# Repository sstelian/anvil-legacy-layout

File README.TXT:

This repository includes the 3 boards designed for the Anvil sumo robot by Stelian Saracut and Virgil Litan in 2016.

The motor driver board is not functional. The other 2 boards are tested and were previously used on our robot.

Build these boards on your own risk. We do not take responsibility for any damage related to building or using these designs.

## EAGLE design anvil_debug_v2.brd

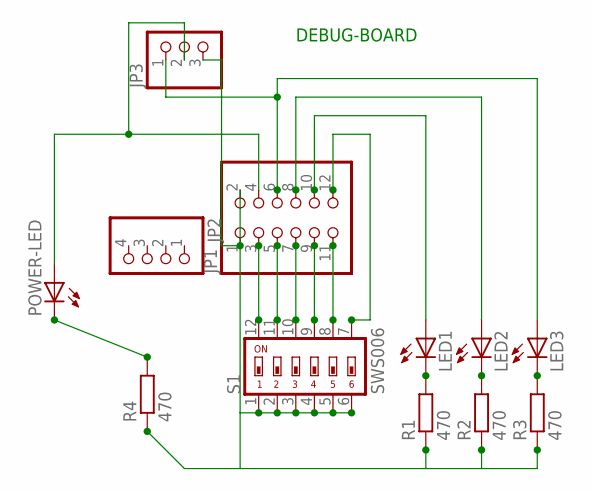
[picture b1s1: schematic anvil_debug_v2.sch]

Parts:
JP1: PINHD-2X6; 2X06
JP2: PINHD-1X4; 1X04
JP3: PINHD-1X3; 1X03
LED1, LED2, LED3: LEDSMT1206; 1206
POWER-LED: LEDSMT1206; 1206
R1, R2, R3, R4: 470; R1206
S1: SWS006; SMS-006

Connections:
unnamed: LED1.C, R1.2
unnamed: LED2.C, R2.2
unnamed: LED3.C, R3.2
unnamed: JP1.3, S1.12
unnamed: JP1.5, S1.11
unnamed: JP1.7, S1.10
unnamed: JP1.9, S1.9
unnamed: JP1.11, S1.8
unnamed: JP1.12, S1.7
unnamed: JP1.10, LED1.A
unnamed: JP1.8, LED2.A
unnamed: JP1.1, JP1.2, JP3.3, R1.1, R2.1, R3.1, R4.1, S1.1, S1.2, S1.3, S1.4, S1.5, S1.6
unnamed: JP1.6, JP3.1, LED3.A
unnamed: POWER-LED.C, R4.2
unnamed: JP1.4, JP3.2, POWER-LED.A

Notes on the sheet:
DEBUG-BOARD

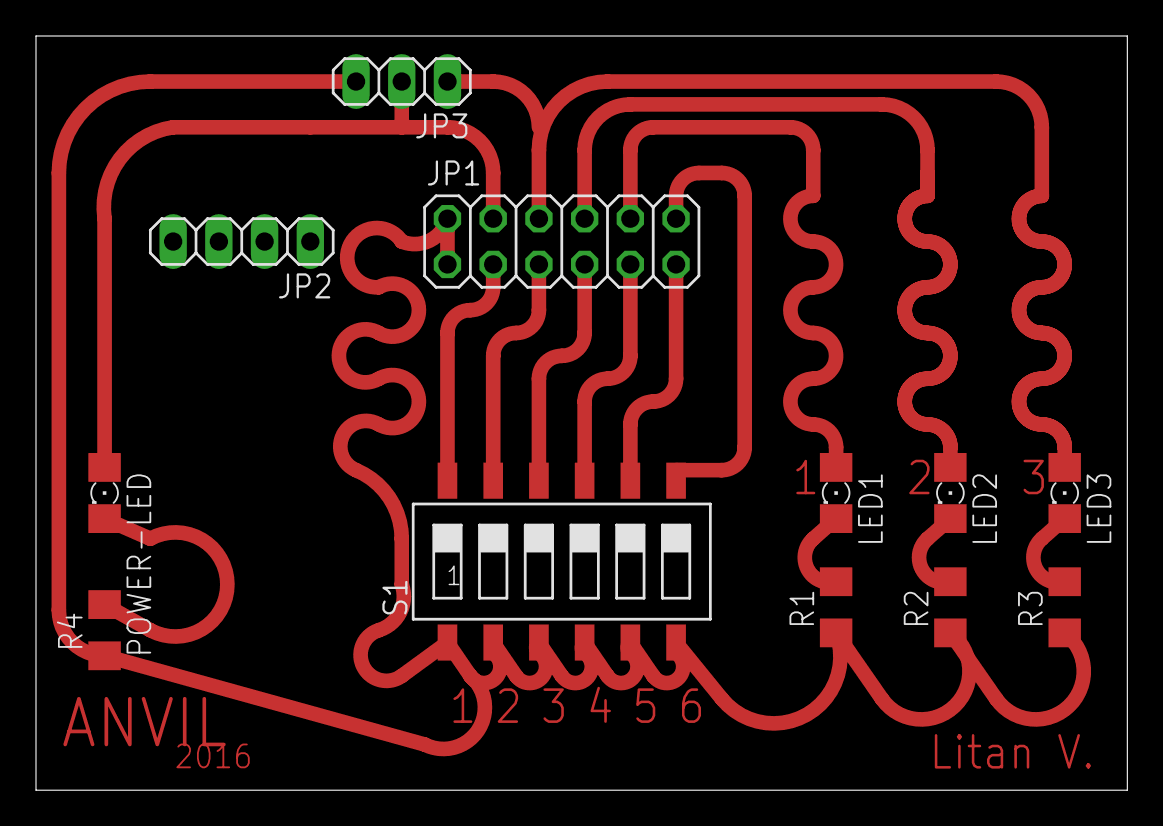
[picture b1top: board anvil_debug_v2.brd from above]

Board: 2 copper layers, 60.6 x 41.9 mm, 12 parts (0 on the bottom side), 15 nets.

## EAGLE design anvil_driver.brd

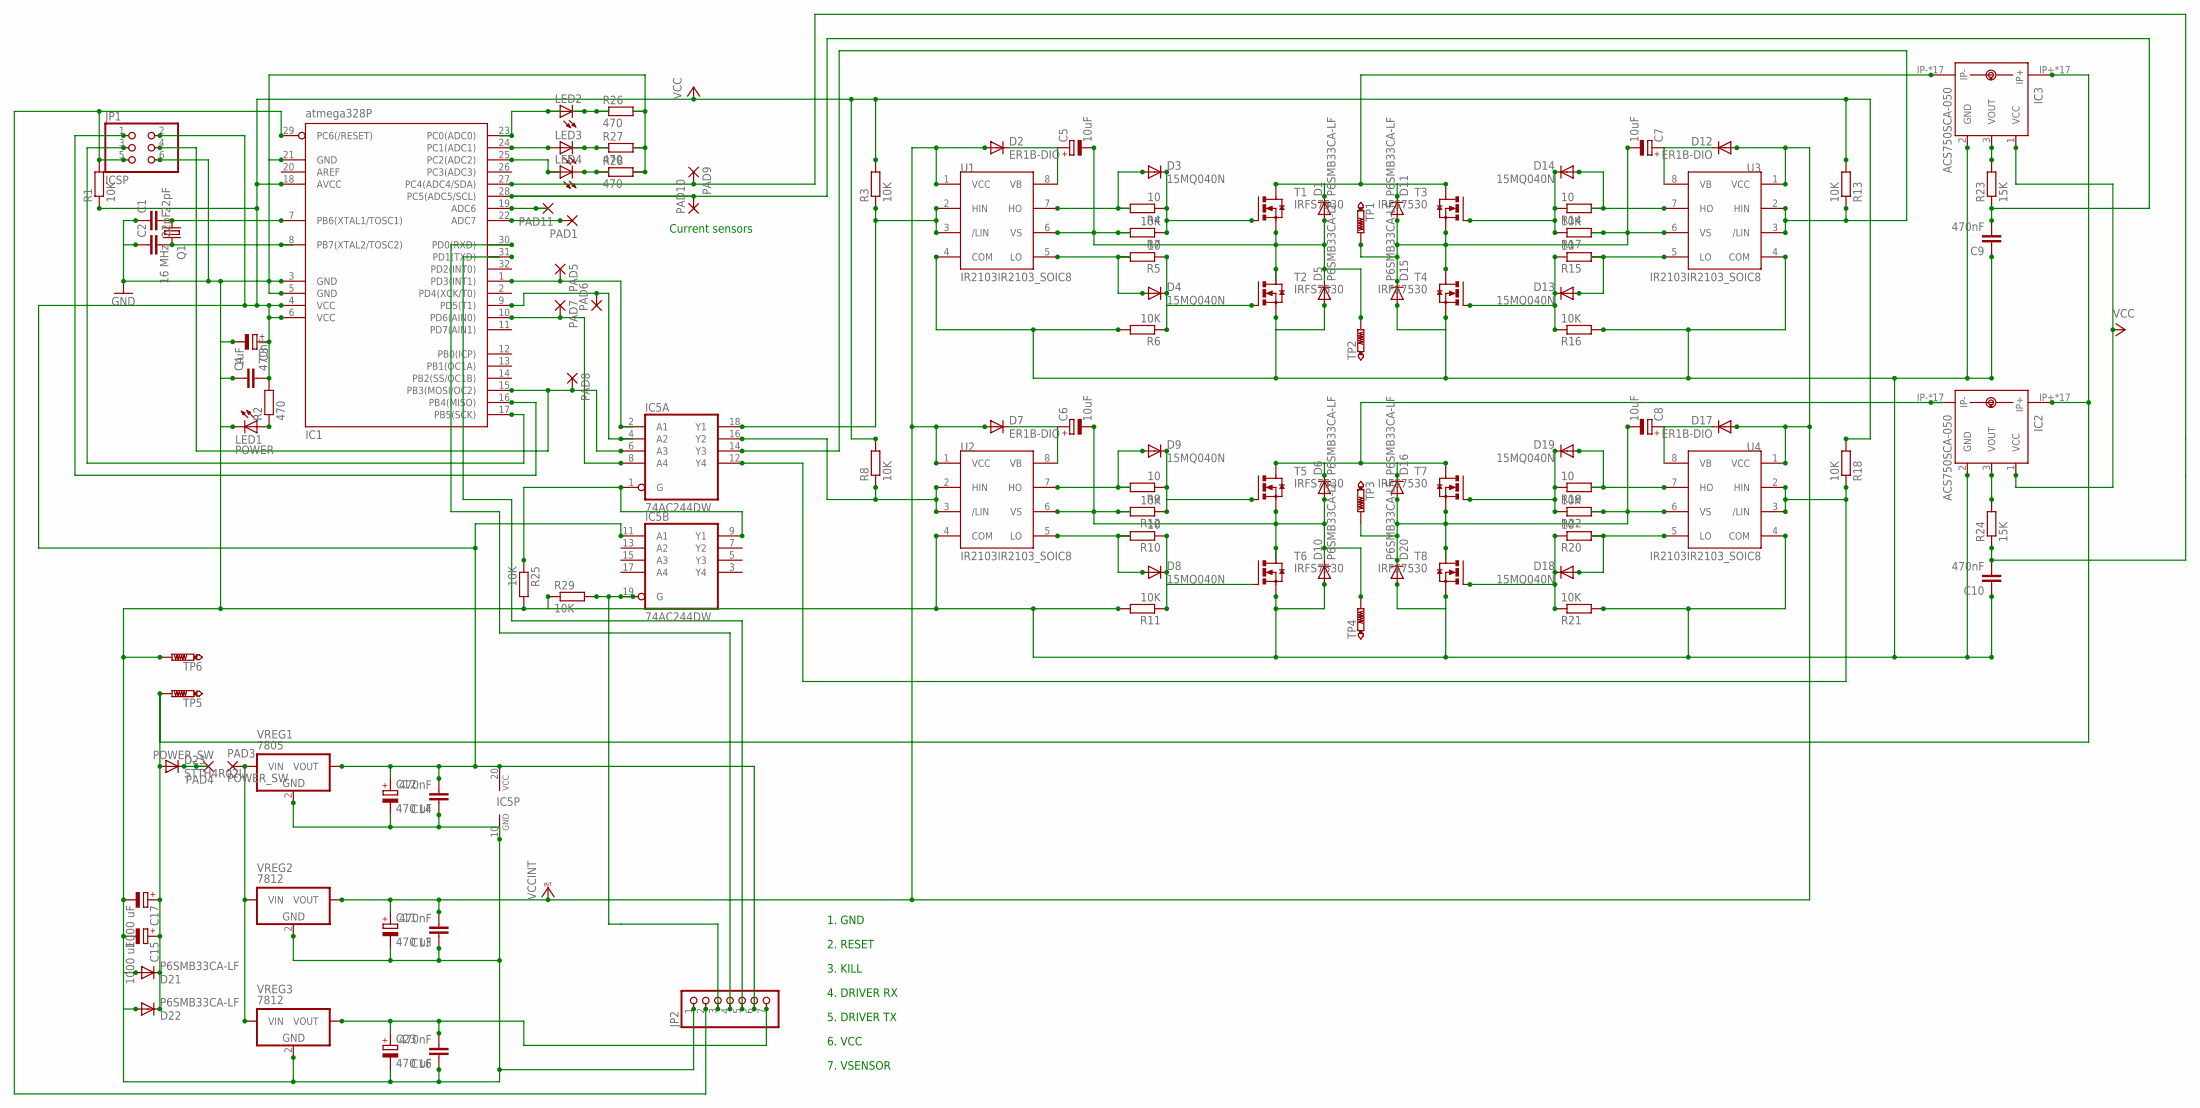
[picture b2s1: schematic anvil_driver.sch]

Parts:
C1, C2: 22pF; C1206
C3: 1uF; 153CLV-0405
C4, C9, C10, C13, C14, C16: 470nF; C1206
C5, C6, C7, C8: 10uF; 153CLV-0405
C11, C12, C23: 470 uF; 139CLL-2W
C15, C17: 1000 uF; 139CLL-2W
D1, D5, D6, D10, D11, D15, D16, D20, D21, D22: P6SMB33CA-LF; DO214AA
D2, D7, D12, D17: ER1B-DIO; DO214AC
D3, D4, D8, D9, D13, D14, D18, D19: 15MQ040N; DO214AC
D23: STTH4R02U; DO214AA
IC1: atmega328P; TQFP32-08
IC2, IC3: ACS750SCA-050; ACS75050
IC5: 74AC244DW; SO20W
JP1: ICSP; 2X03SMD
JP2: PINHD-1X7_2.54; 1X07
LED1: POWER; 1206
LED2, LED3, LED4: LEDSMT1206; 1206
PAD1, PAD5, PAD6, PAD7, PAD8, PAD9, PAD10, PAD11: SMD2; SMD1,27-2,54
PAD3, PAD4: POWER_SW; 1,6/0,8
Q1: 16 MHz; CSM-7X-DU
R1, R3, R6, R7, R8, R11, R12, R13, R16, R17, R18, R21, R22, R25, R29: 10K; M1206
R2, R26, R27, R28: 470; M1206
R4, R5, R9, R10, R14, R15, R19, R20: 10; M1206
R23, R24: 15K; M1206
T1, T2, T3, T4, T5, T6, T7, T8: IRFS7530; DDPAK7
TP1, TP2, TP3, TP4, TP5, TP6: PTR1PAD1-20; P1-20
U1, U2, U3, U4: IR2103IR2103_SOIC8; SO08
VREG1: 7805; D2PAK
VREG2, VREG3: 7812; D2PAK

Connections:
GND: C1.1, C2.1, C3.-, C4.1, C9.1, C10.1, C11.-, C12.-, C13.1, C14.1, C15.-, C16.1, C17.-, C23.-, D5.A, D10.A, D15.A, D20.A, D21.A, D22.A, IC1.3 (GND), IC1.5 (GND), IC1.21 (GND), IC2.2 (GND), IC3.2 (GND), IC5.10 (GND), JP1.6, JP2.1, LED1.C, R6.2, R11.2, R16.2, R21.2, R25.2, R26.2, R27.2, R28.2, R29.1, T2.2 (S), T2.3 (S), T2.5 (S), T2.6 (S), T2.7 (S), T4.2 (S), T4.3 (S), T4.5 (S), T4.6 (S), T4.7 (S), T6.2 (S), T6.3 (S), T6.5 (S), T6.6 (S), T6.7 (S), T8.2 (S), T8.3 (S), T8.5 (S), T8.6 (S), T8.7 (S), TP6.TP, U1.4 (COM), U2.4 (COM), U3.4 (COM), U4.4 (COM), VREG1.2 (GND), VREG2.2 (GND), VREG3.2 (GND)
unnamed: D1.C, D11.C, IC3.IP-, IC3.IP-@2 (IP-), IC3.IP-@3 (IP-), IC3.IP-@4 (IP-), IC3.IP-@5 (IP-), IC3.IP-@6 (IP-), IC3.IP-@7 (IP-), IC3.IP-@8 (IP-), IC3.IP-@9 (IP-), IC3.IP-@10 (IP-), IC3.IP-@11 (IP-), IC3.IP-@12 (IP-), IC3.IP-@13 (IP-), IC3.IP-@14 (IP-), IC3.IP-@15 (IP-), IC3.IP-@16 (IP-), IC3.IP-@17 (IP-), T1.4 (D), T3.4 (D)
unnamed: IC5.18 (Y1), R3.1, U1.2 (HIN), U1.3 (/LIN)
unnamed: IC1.24 (PC1(ADC1)), LED3.A
unnamed: IC1.1 (PD3(INT1)), IC5.2 (A1), PAD5.1
unnamed: IC1.16 (PB4(MISO)), JP1.1
unnamed: IC1.17 (PB5(SCK)), JP1.3
unnamed: C1.2, IC1.7 (PB6(XTAL1/TOSC1)), Q1.1
unnamed: C2.2, IC1.8 (PB7(XTAL2/TOSC2)), Q1.2
unnamed: C5.-, D1.A, D5.C, R7.2, T1.2 (S), T1.3 (S), T1.5 (S), T1.6 (S), T1.7 (S), T2.4 (D), TP2.TP, U1.6 (VS)
unnamed: LED1.A, R2.1
unnamed: D3.A, R4.2, U1.7 (HO)
unnamed: D4.A, R5.2, U1.5 (LO)
unnamed: D4.C, R5.1, R6.1, T2.1 (G)
unnamed: D3.C, R4.1, R7.1, T1.1 (G)
unnamed: C15.+, C17.+, D21.C, D22.C, D23.A, IC2.IP+, IC2.IP+@2 (IP+), IC2.IP+@3 (IP+), IC2.IP+@4 (IP+), IC2.IP+@5 (IP+), IC2.IP+@6 (IP+), IC2.IP+@7 (IP+), IC2.IP+@8 (IP+), IC2.IP+@9 (IP+), IC2.IP+@10 (IP+), IC2.IP+@11 (IP+), IC2.IP+@12 (IP+), IC2.IP+@13 (IP+), IC2.IP+@14 (IP+), IC2.IP+@15 (IP+), IC2.IP+@16 (IP+), IC2.IP+@17 (IP+), IC3.IP+, IC3.IP+@2 (IP+), IC3.IP+@3 (IP+), IC3.IP+@4 (IP+), IC3.IP+@5 (IP+), IC3.IP+@6 (IP+), IC3.IP+@7 (IP+), IC3.IP+@8 (IP+), IC3.IP+@9 (IP+), IC3.IP+@10 (IP+), IC3.IP+@11 (IP+), IC3.IP+@12 (IP+), IC3.IP+@13 (IP+), IC3.IP+@14 (IP+), IC3.IP+@15 (IP+), IC3.IP+@16 (IP+), IC3.IP+@17 (IP+), TP5.TP
unnamed: IC5.16 (Y2), R8.1, U2.2 (HIN), U2.3 (/LIN)
unnamed: D6.C, D16.C, IC2.IP-, IC2.IP-@2 (IP-), IC2.IP-@3 (IP-), IC2.IP-@4 (IP-), IC2.IP-@5 (IP-), IC2.IP-@6 (IP-), IC2.IP-@7 (IP-), IC2.IP-@8 (IP-), IC2.IP-@9 (IP-), IC2.IP-@10 (IP-), IC2.IP-@11 (IP-), IC2.IP-@12 (IP-), IC2.IP-@13 (IP-), IC2.IP-@14 (IP-), IC2.IP-@15 (IP-), IC2.IP-@16 (IP-), IC2.IP-@17 (IP-), T5.4 (D), T7.4 (D)
unnamed: C6.-, D6.A, D10.C, R12.2, T5.2 (S), T5.3 (S), T5.5 (S), T5.6 (S), T5.7 (S), T6.4 (D), TP4.TP, U2.6 (VS)
unnamed: D9.A, R9.2, U2.7 (HO)
unnamed: D8.A, R10.2, U2.5 (LO)
unnamed: D8.C, R10.1, R11.1, T6.1 (G)
unnamed: D9.C, R9.1, R12.1, T5.1 (G)
unnamed: C9.2, IC1.28 (PC5(ADC5/SCL)), PAD10.1, R23.1
unnamed: IC3.3 (VOUT), R23.2
unnamed: IC5.14 (Y3), R13.1, U3.2 (HIN), U3.3 (/LIN)
unnamed: C7.-, D11.A, D15.C, R17.2, T3.2 (S), T3.3 (S), T3.5 (S), T3.6 (S), T3.7 (S), T4.4 (D), TP1.TP, U3.6 (VS)
unnamed: D14.A, R14.2, U3.7 (HO)
unnamed: D13.A, R15.2, U3.5 (LO)
unnamed: D13.C, R15.1, R16.1, T4.1 (G)
unnamed: D14.C, R14.1, R17.1, T3.1 (G)
unnamed: C10.2, IC1.27 (PC4(ADC4/SDA)), PAD9.1, R24.1
unnamed: D23.C, PAD4.1
unnamed: IC1.9 (PD5(T1)), IC5.4 (A2), PAD6.1
unnamed: C8.-, D16.A, D20.C, R22.2, T7.2 (S), T7.3 (S), T7.5 (S), T7.6 (S), T7.7 (S), T8.4 (D), TP3.TP, U4.6 (VS)
unnamed: D19.A, R19.2, U4.7 (HO)
unnamed: D18.A, R20.2, U4.5 (LO)
unnamed: D18.C, R20.1, R21.1, T8.1 (G)
unnamed: D19.C, R19.1, R22.1, T7.1 (G)
unnamed: C16.2, C23.+, JP2.7, VREG3.3 (VOUT)
unnamed: IC1.15 (PB3(MOSI/OC2)), IC5.6 (A3), JP1.4, PAD8.1
unnamed: IC1.10 (PD6(AIN0)), IC5.8 (A4), PAD7.1
unnamed: LED2.C, R26.1
unnamed: IC5.12 (Y4), R18.1, U4.2 (HIN), U4.3 (/LIN)
unnamed: LED3.C, R27.1
unnamed: IC1.19 (ADC6), PAD11.1
unnamed: IC1.23 (PC0(ADC0)), LED2.A
unnamed: LED4.C, R28.1
unnamed: IC1.25 (PC2(ADC2)), LED4.A
unnamed: PAD3.1, VREG1.1 (VIN), VREG2.1 (VIN), VREG3.1 (VIN)
unnamed: IC2.3 (VOUT), R24.2
unnamed: IC1.30 (PD0(RXD)), JP2.4
unnamed: IC5.1 (G), IC5.9 (Y1), R25.1
unnamed: IC5.19 (G), JP2.3, R29.2
unnamed: IC1.22 (ADC7), PAD1.1
RESET: IC1.29 (PC6(/RESET)), JP1.5, JP2.2, R1.2
VB_1: C5.+, D2.C, U1.8 (VB)
VB_2: C7.+, D12.C, U3.8 (VB)
VB_3: C8.+, D17.C, U4.8 (VB)
VB_4: C6.+, D7.C, U2.8 (VB)
VCC: C3.+, C4.2, C12.+, C14.2, IC1.4 (VCC), IC1.6 (VCC), IC1.18 (AVCC), IC2.1 (VCC), IC3.1 (VCC), IC5.11 (A1), IC5.20 (VCC), JP1.2, JP2.6, R1.1, R2.2, R3.2, R8.2, R13.2, R18.2, VREG1.3 (VOUT)
VCCINT: C11.+, C13.2, D2.A, D7.A, D12.A, D17.A, U1.1 (VCC), U2.1 (VCC), U3.1 (VCC), U4.1 (VCC), VREG2.3 (VOUT)

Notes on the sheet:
Current sensors
1. GND
2. RESET
3. KILL
4. DRIVER RX
5. DRIVER TX
6. VCC
7. VSENSOR

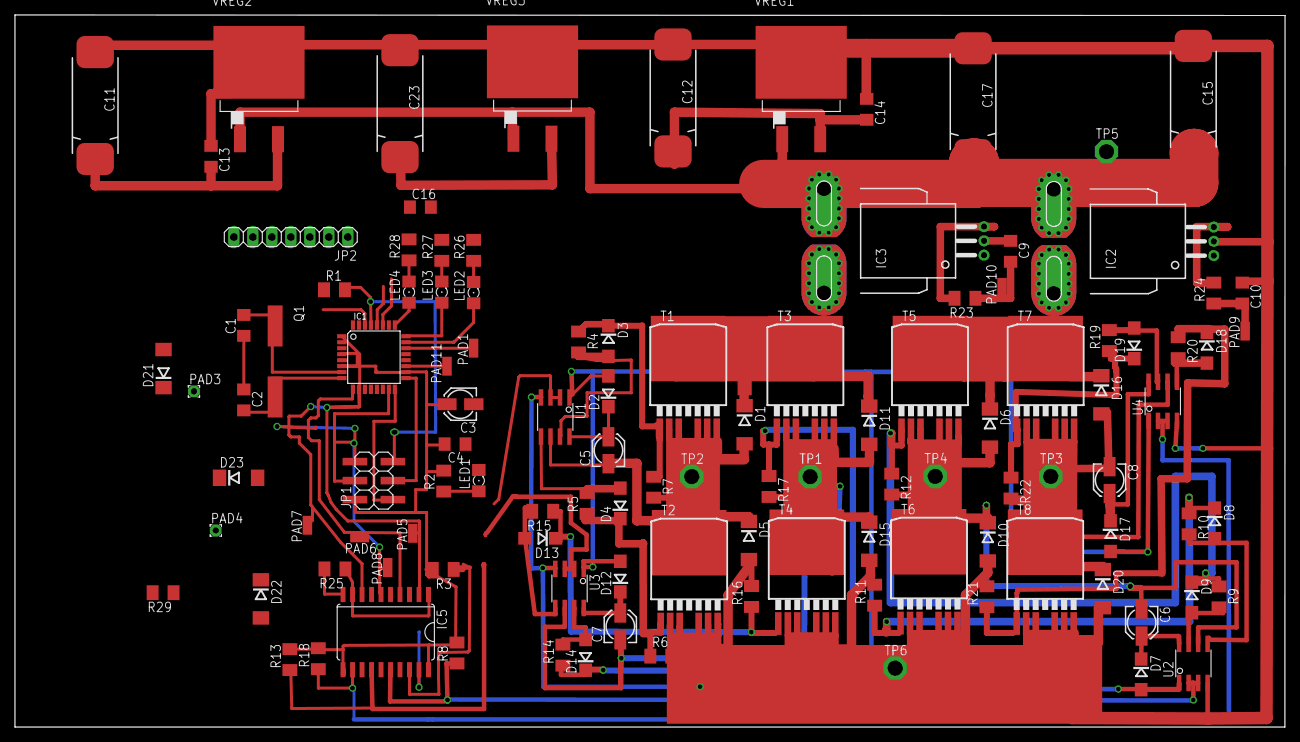
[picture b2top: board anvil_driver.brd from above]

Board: 2 copper layers, 169.9 x 95.2 mm, 112 parts (0 on the bottom side), 62 nets.

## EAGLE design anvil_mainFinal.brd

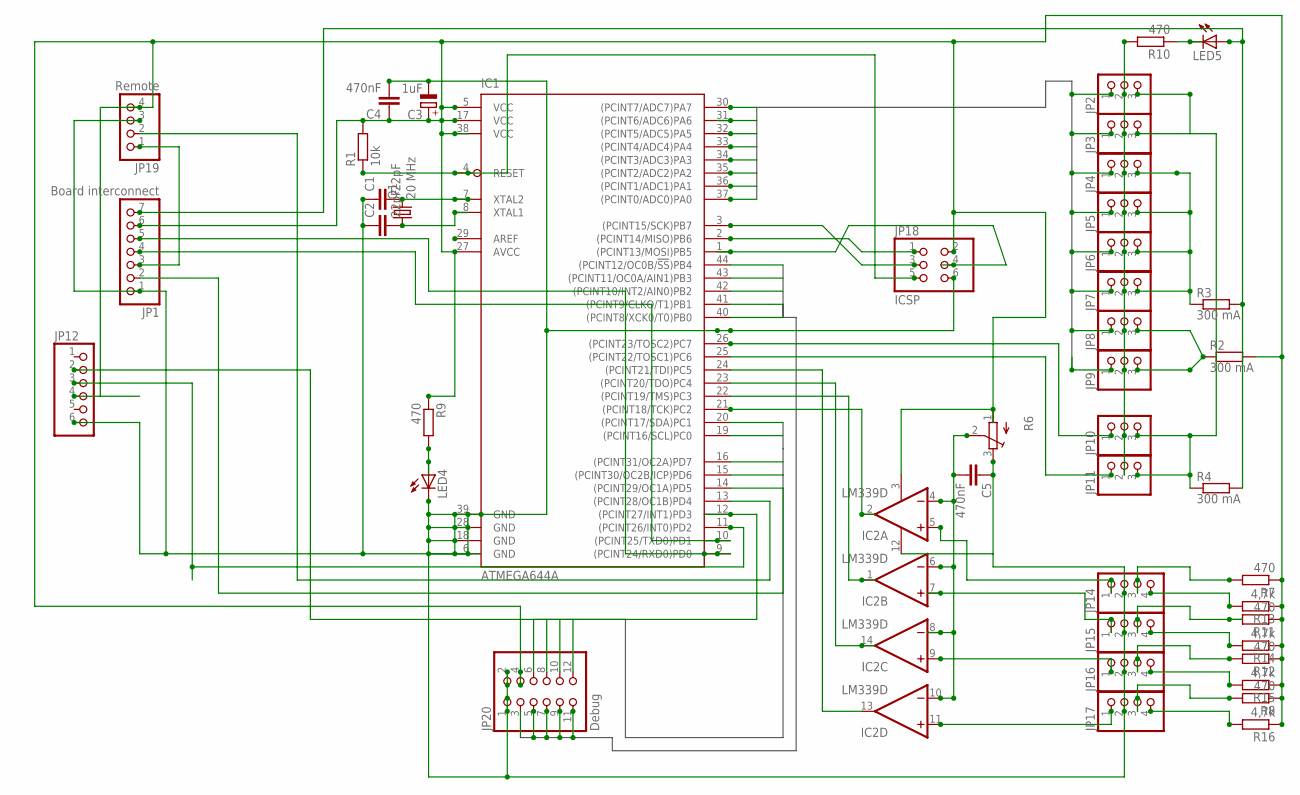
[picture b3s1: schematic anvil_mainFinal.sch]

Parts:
C1, C2: 22pF; C1206
C3: 1uF; 153CLV-0505
C4, C5: 470nF; C1206
IC1: ATMEGA644A; TQFP44
IC2: LM339D; SO14
JP1: Board interconnect; 1X07
JP2, JP3, JP4, JP5, JP6, JP7, JP8, JP9, JP10, JP11: PINHD-1X3_2.54-SMD; 1X03SMD
JP12: PINHD-1X61X06_SMT; 1X06_SMT
JP14, JP15, JP16, JP17: PINHD-1X4_2.54-SMD; 1X04SMD
JP18: ICSP; 2X03SMD
JP19: Remote; 1X04SMD
JP20: Debug; 2X06SMD
LED4, LED5: LEDSMT1206; 1206
Q1: 20 MHz; CSM-7X-DU
R1: 10k; R1206
R2, R3, R4: 300 mA; SMS-REF
R6: TRIM_EU-SM-42/43B; SM-42/43B
R7, R8, R9, R10, R11, R12: 470; R1206
R13, R14, R15, R16: 4,7k; R1206

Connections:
DBG0: IC1.20 ((PCINT17/SDA)PC1), JP20.12
DBG1: IC1.19 ((PCINT16/SCL)PC0), JP20.10
DBG2: IC1.16 ((PCINT31/OC2A)PD7), JP20.8
DBG3: IC1.15 ((PCINT30/OC2B/ICP)PD6), JP20.6
DBG4: IC1.44 ((PCINT12/OC0B/!SS!)PB4), JP20.3
DBG5: IC1.43 ((PCINT11/OC0A/AIN1)PB3), JP20.5
DBG6: IC1.42 ((PCINT10/INT2/AIN0)PB2), JP20.7
DBG7: IC1.41 ((PCINT9/CLKO/T1)PB1), JP20.9
DBG8: IC1.40 ((PCINT8/XCK0/T0)PB0), JP20.11
GND: C1.1, C2.1, C3.-, C4.2, C5.1, IC1.6 (GND), IC1.18 (GND), IC1.28 (GND), IC1.39 (GND), IC2.12 (GND), JP1.1, JP2.2, JP3.2, JP4.2, JP5.2, JP6.2, JP7.2, JP8.2, JP9.2, JP10.2, JP11.2, JP12.6, JP14.2, JP15.2, JP16.2, JP17.2, JP18.6, JP19.3, JP20.1, JP20.2, LED4.C, R6.3 (E), R10.2
unnamed: IC1.11 ((PCINT26/INT0)PD2), JP12.3
unnamed: IC2.11 (+IN), JP17.1
unnamed: C1.2, IC1.7 (XTAL2), Q1.2
unnamed: C2.2, IC1.8 (XTAL1), Q1.1
unnamed: JP14.3, R7.2
unnamed: IC1.4 (RESET), JP18.5, R1.1
unnamed: IC2.9 (+IN), JP16.1
unnamed: IC1.24 ((PCINT21/TDI)PC5), IC2.13 (OUT)
unnamed: IC1.13 ((PCINT28/OC1B)PD4), JP19.2
unnamed: IC1.21 ((PCINT18/TCK)PC2), IC2.2 (OUT)
unnamed: IC1.12 ((PCINT27/INT1)PD3), JP12.2
unnamed: IC1.22 ((PCINT19/TMS)PC3), IC2.1 (OUT)
unnamed: IC1.14 ((PCINT29/OC1A)PD5), JP1.2
unnamed: JP8.3, JP9.3, R2.2
unnamed: JP1.7, LED5.A, R3.1, R4.1
unnamed: IC2.7 (+IN), JP15.1
unnamed: IC1.3 ((PCINT15/SCK)PB7), JP18.3
unnamed: IC1.2 ((PCINT14/MISO)PB6), JP18.1
unnamed: IC1.1 ((PCINT13/MOSI)PB5), JP18.4
unnamed: IC2.5 (+IN), JP14.1
unnamed: C5.2, IC2.4 (-IN), IC2.6 (-IN), IC2.8 (-IN), IC2.10 (-IN), R6.2 (S)
unnamed: JP14.4, R13.2
unnamed: JP15.3, R11.2
unnamed: IC1.26 ((PCINT23/TOSC2)PC7), JP10.1
unnamed: IC1.25 ((PCINT22/TOSC1)PC6), JP11.1
unnamed: IC1.23 ((PCINT20/TDO)PC4), IC2.14 (OUT)
unnamed: JP15.4, R14.2
unnamed: JP4.3, JP5.3, JP6.3, JP7.3, R3.2
unnamed: JP2.3, JP3.3, JP10.3, JP11.3, R4.2
unnamed: C3.+, C4.1, IC1.5 (VCC), IC1.17 (VCC), IC1.27 (AVCC), IC1.38 (VCC), IC2.3 (V+), JP1.6, JP12.4, JP18.2, JP19.4, JP20.4, R1.2, R2.1, R6.1 (A), R7.1, R8.1, R9.1, R11.1, R12.1, R13.1, R14.1, R15.1, R16.1
unnamed: JP16.3, R12.2
unnamed: JP16.4, R15.2
unnamed: IC1.10 ((PCINT25/TXD0)PD1), JP1.4
unnamed: IC1.9 ((PCINT24/RXD0)PD0), JP1.5
unnamed: JP17.3, R8.2
unnamed: JP17.4, R16.2
unnamed: JP1.3, JP19.1
unnamed: LED4.A, R9.2
unnamed: LED5.C, R10.1
SNS0: IC1.30 ((PCINT7/ADC7)PA7), JP2.1
SNS1: IC1.31 ((PCINT6/ADC6)PA6), JP3.1
SNS2: IC1.32 ((PCINT5/ADC5)PA5), JP4.1
SNS3: IC1.33 ((PCINT4/ADC4)PA4), JP5.1
SNS4: IC1.34 ((PCINT3/ADC3)PA3), JP6.1
SNS5: IC1.35 ((PCINT2/ADC2)PA2), JP7.1
SNS6: IC1.36 ((PCINT1/ADC1)PA1), JP8.1
SNS7: IC1.37 ((PCINT0/ADC0)PA0), JP9.1

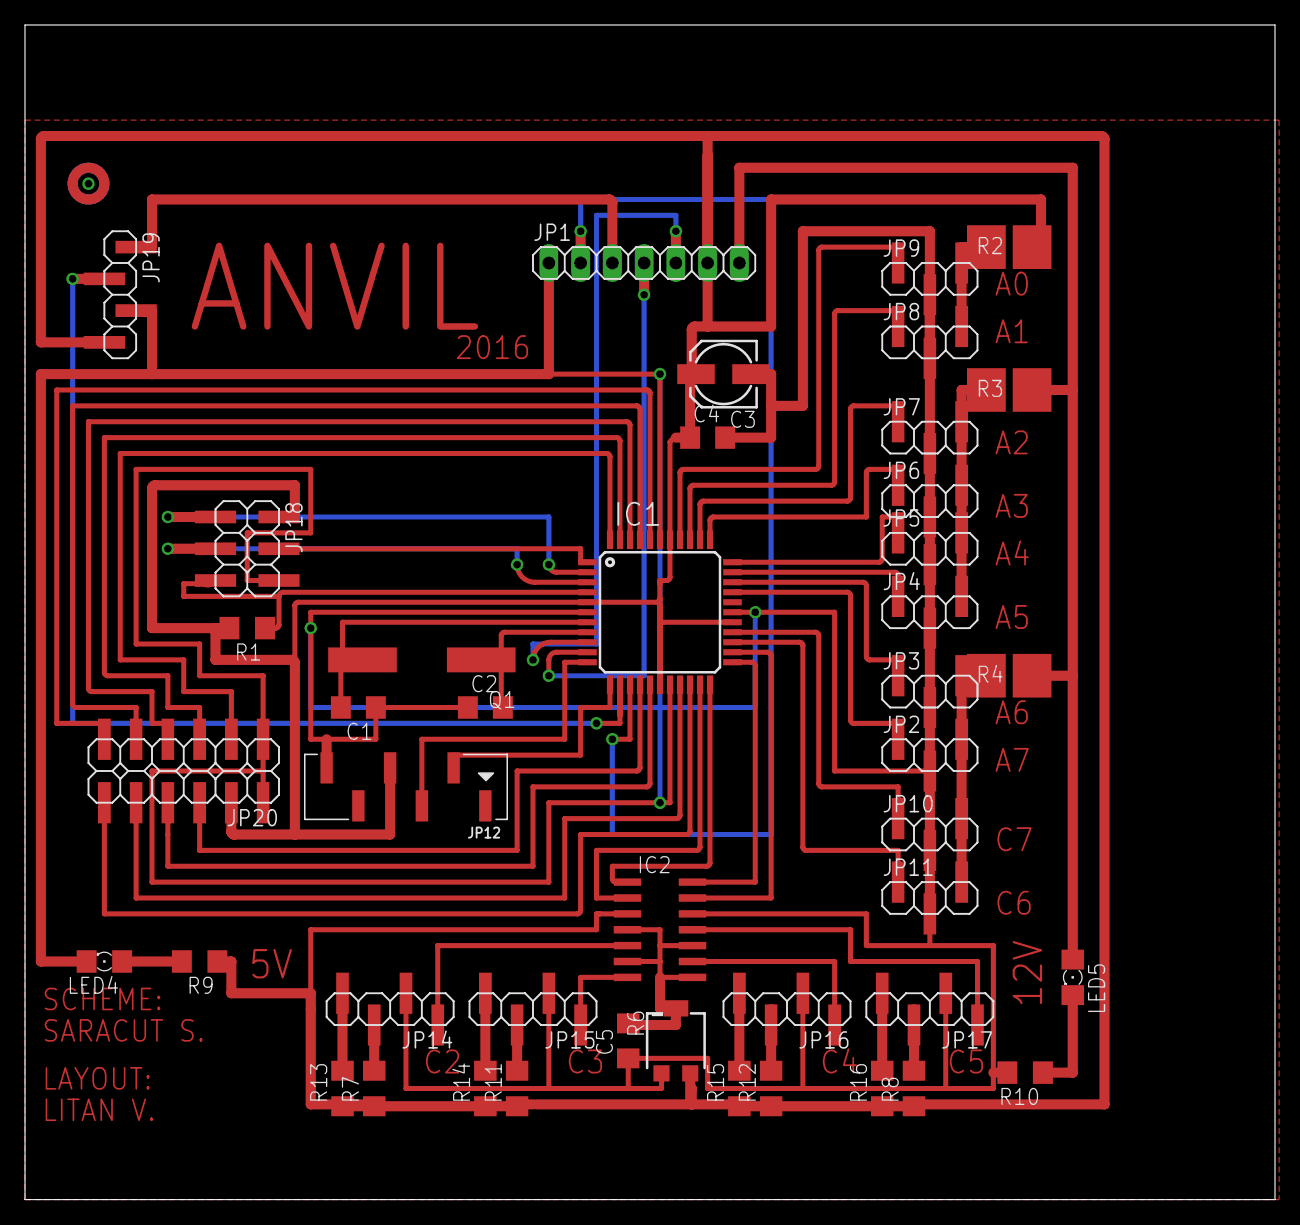
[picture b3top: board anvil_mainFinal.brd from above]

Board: 2 copper layers, 100.0 x 94.0 mm, 44 parts (0 on the bottom side), 57 nets.
